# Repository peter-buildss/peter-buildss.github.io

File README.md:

# Peter Perez - Fab Academy documentation

Right now this is a clone of my Fab Academy site, but will evolve into my personal website.

Visit [fabacademy.org](https://fabacademy.org/) for class and other information.

Good day and welcome to Peter Perez's Fab Academy Portfolio and more. Here we will be tracking my journey with the Moonlighter Fablab through this program. 

This website was coded simply using HTML, CSS, some help from ChatGPT and Dall-E and a lot of elbow grease. 

I hope you like what you see and learn with me!

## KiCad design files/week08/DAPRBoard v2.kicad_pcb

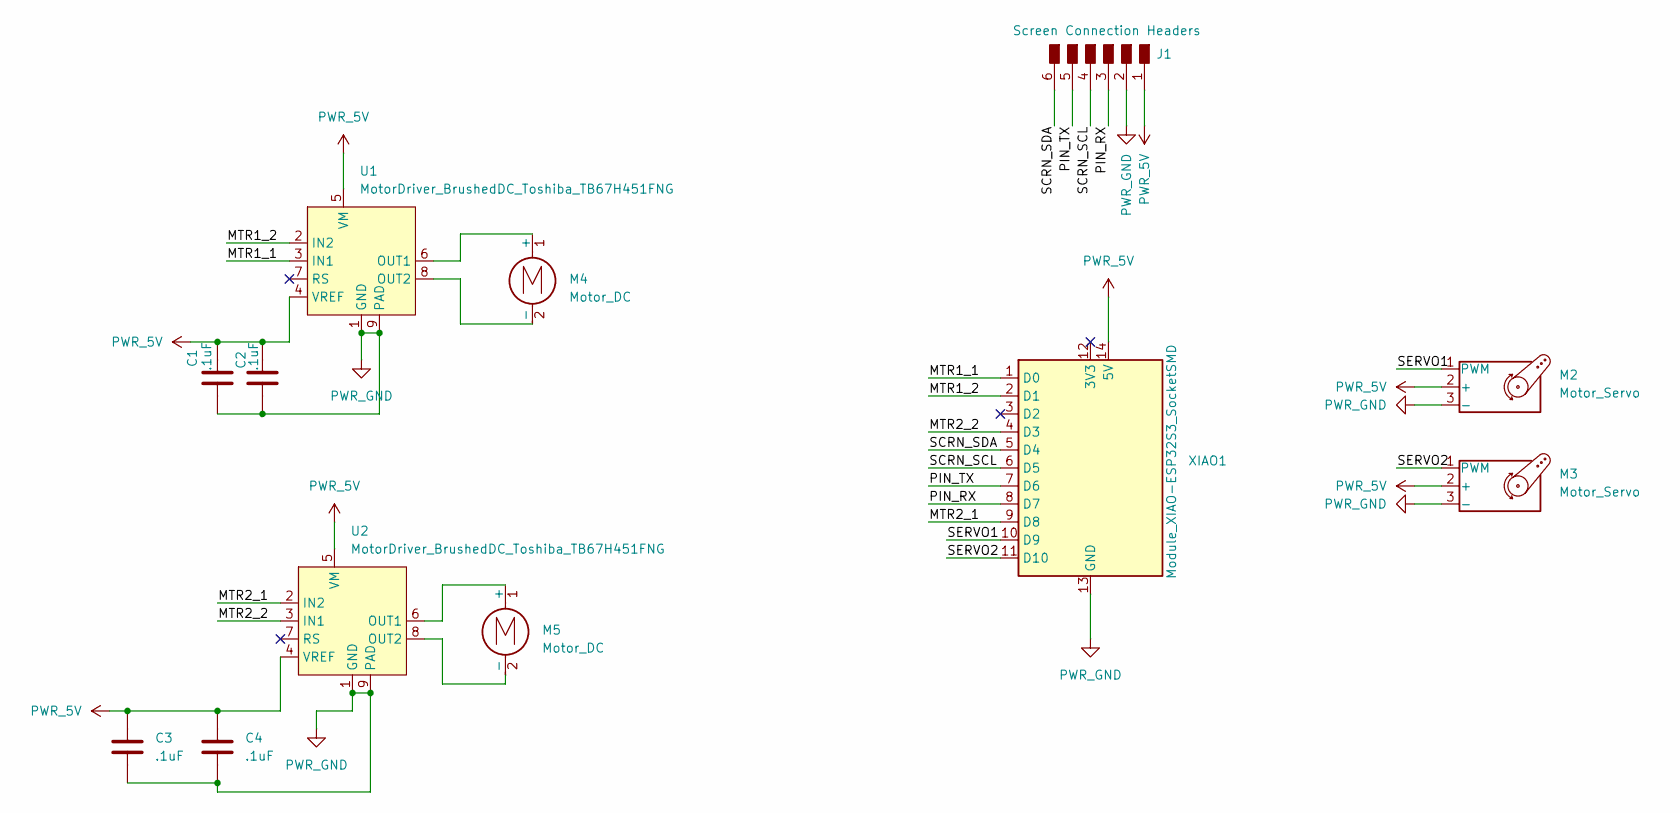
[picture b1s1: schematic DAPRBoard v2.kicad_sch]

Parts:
C1, C2, C3, C4: .1uF; C_1206
J1: Screen Connection Headers; PinHeader_1x06_P2.54mm_Horizontal_SMD
M2, M3: Motor_Servo; PinSocket_1x03_P2.54mm_Vertical_SMD
M4, M5: Motor_DC; PinSocket_1x02_P2.54mm_Vertical_SMD
U1, U2: MotorDriver_BrushedDC_Toshiba_TB67H451FNG; HSOP-8
XIAO1: Module_XIAO-ESP32S3_SocketSMD; SeeedStudio_XIAO_SocketSMD

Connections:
/MTR1_1: U1.3 (IN1), XIAO1.1 (D0)
/MTR1_2: U1.2 (IN2), XIAO1.2 (D1)
/MTR2_1: U2.2 (IN2), XIAO1.9 (D8)
/MTR2_2: U2.3 (IN1), XIAO1.4 (D3)
/PIN_RX: J1.3, XIAO1.8 (D7)
/PIN_TX: J1.5, XIAO1.7 (D6)
/SCRN_SCL: J1.4, XIAO1.6 (D5)
/SCRN_SDA: J1.6, XIAO1.5 (D4)
/SERVO1: M2.1 (PWM), XIAO1.10 (D9)
/SERVO2: M3.1 (PWM), XIAO1.11 (D10)
unnamed: M4.1 (+), U1.6 (OUT1)
unnamed: M4.2 (-), U1.8 (OUT2)
unnamed: M5.1 (+), U2.6 (OUT1)
unnamed: M5.2 (-), U2.8 (OUT2)
PWR_5V: C1.1, C2.1, C3.1, C4.1, J1.1, M2.2 (+), M3.2 (+), U1.4 (VREF), U1.5 (VM), U2.4 (VREF), U2.5 (VM), XIAO1.14 (5V)
PWR_GND: C1.2, C2.2, C3.2, C4.2, J1.2, M2.3 (-), M3.3 (-), U1.1 (GND), U1.9 (PAD), U2.1 (GND), U2.9 (PAD), XIAO1.13 (GND)

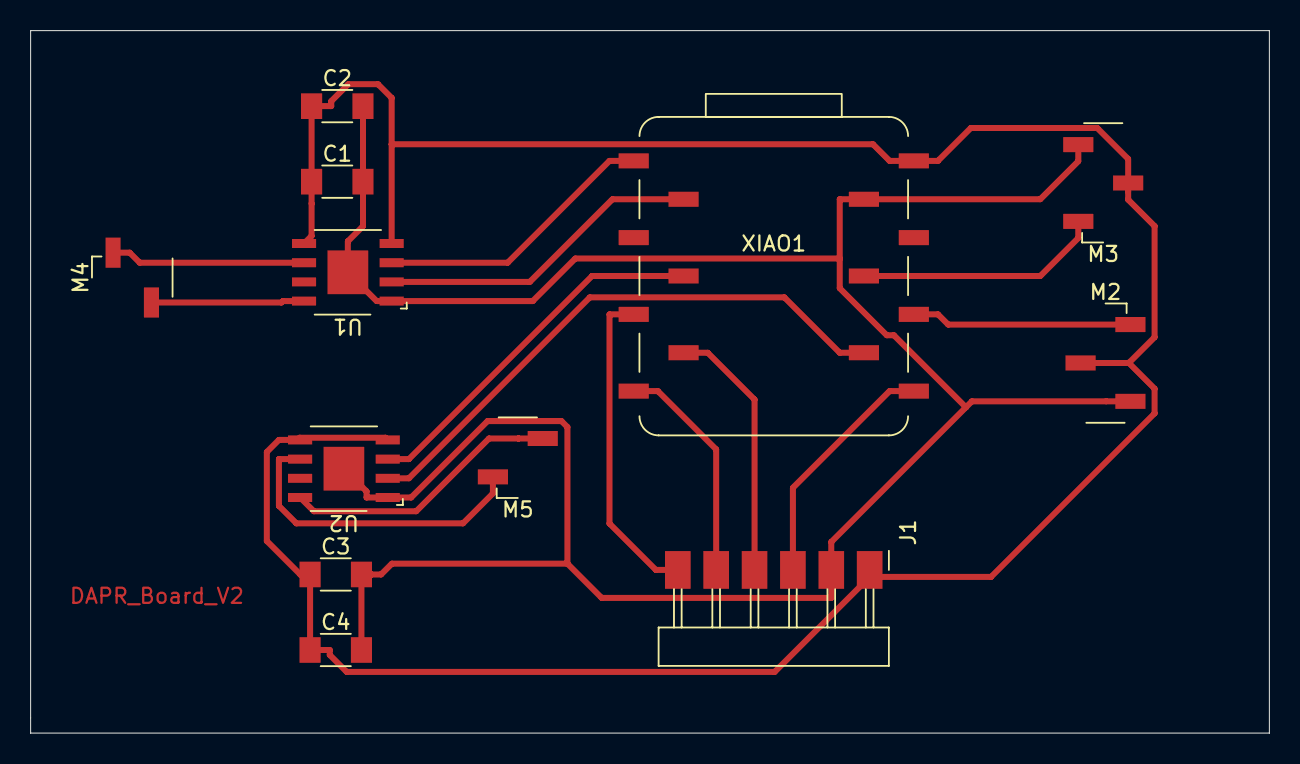
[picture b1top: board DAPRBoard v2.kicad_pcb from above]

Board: 2 copper layers, 82.0 x 46.5 mm, 12 parts (0 on the bottom side), 16 nets.

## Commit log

2024-02-01 Backing up and hosting GitlabSite on Github
    New commit for perezrobotics.com
2024-02-01 Create CNAME
2024-08-28 Perez FabAcademy Backup
2024-08-28 Initial Page update
2024-09-24 adding mentored projects
2024-09-24 Mentored Project update 2
2024-09-26 added http to the sites, see if links work
2024-09-26 Add image to projects page
2024-12-02 Website Updates 1
2024-12-06 Creating outline of site
2025-04-08 Fixing titles
2025-04-14 modification?
2025-05-20 Magis-et-Ingenium Edits
2025-05-20 Guild Register Added
2025-09-04 Add external links and unify navigation
2025-10-07 Updating website branding to match new Peter Builds
2025-10-08 Updated all student websites
